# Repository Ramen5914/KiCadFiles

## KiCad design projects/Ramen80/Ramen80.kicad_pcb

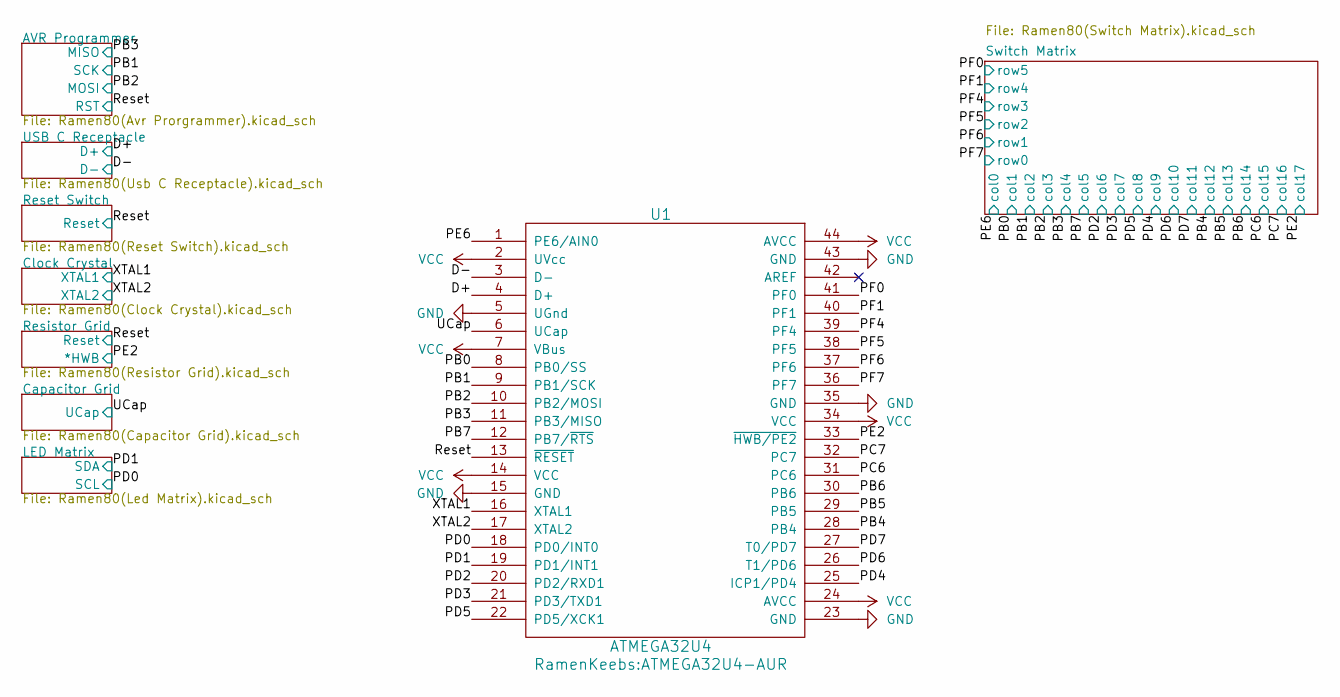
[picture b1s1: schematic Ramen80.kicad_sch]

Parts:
U1: ATMEGA32U4; ATMEGA32U4-AUR

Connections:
/D+: U1.4 (D+); also elsewhere on the board
/D-: U1.3 (D-); also elsewhere on the board
/PB0: U1.8 (PB0/SS); also elsewhere on the board
/PB1: U1.9 (PB1/SCK); also elsewhere on the board
/PB2: U1.10 (PB2/MOSI); also elsewhere on the board
/PB3: U1.11 (PB3/MISO); also elsewhere on the board
/PB4: U1.28 (PB4); also elsewhere on the board
/PB5: U1.29 (PB5); also elsewhere on the board
/PB6: U1.30 (PB6); also elsewhere on the board
/PB7: U1.12 (PB7/~RTS); also elsewhere on the board
/PC6: U1.31 (PC6); also elsewhere on the board
/PC7: U1.32 (PC7); also elsewhere on the board
/PD0: U1.18 (PD0/INT0); also elsewhere on the board
/PD1: U1.19 (PD1/INT1); also elsewhere on the board
/PD2: U1.20 (PD2/RXD1); also elsewhere on the board
/PD3: U1.21 (PD3/TXD1); also elsewhere on the board
/PD4: U1.25 (ICP1/PD4); also elsewhere on the board
/PD5: U1.22 (PD5/XCK1); also elsewhere on the board
/PD6: U1.26 (T1/PD6); also elsewhere on the board
/PD7: U1.27 (T0/PD7); also elsewhere on the board
/PE2: U1.33 (~HWB/PE2); also elsewhere on the board
/PE6: U1.1 (PE6/AIN0); also elsewhere on the board
/PF0: U1.41 (PF0); also elsewhere on the board
/PF1: U1.40 (PF1); also elsewhere on the board
/PF4: U1.39 (PF4); also elsewhere on the board
/PF5: U1.38 (PF5); also elsewhere on the board
/PF6: U1.37 (PF6); also elsewhere on the board
/PF7: U1.36 (PF7); also elsewhere on the board
/Reset: U1.13 (~RESET); also elsewhere on the board
/UCap: U1.6 (UCap); also elsewhere on the board
/XTAL1: U1.16 (XTAL1); also elsewhere on the board
/XTAL2: U1.17 (XTAL2); also elsewhere on the board
GND: U1.5 (UGnd), U1.15 (GND), U1.23 (GND), U1.35 (GND), U1.43 (GND); also elsewhere on the board
VCC: U1.2 (UVcc), U1.7 (VBus), U1.14 (VCC), U1.24 (AVCC), U1.34 (VCC), U1.44 (AVCC); also elsewhere on the board

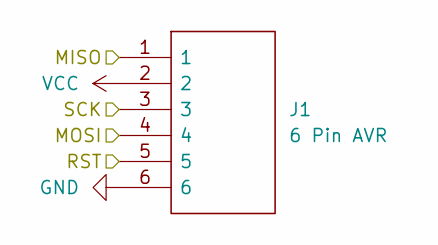
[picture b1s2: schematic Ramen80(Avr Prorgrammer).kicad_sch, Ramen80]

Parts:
J1: 6 Pin AVR; RHDR6W30P0X100_1X6_650X150X210P

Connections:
/PB1: J1.3; also elsewhere on the board
/PB2: J1.4; also elsewhere on the board
/PB3: J1.1; also elsewhere on the board
/Reset: J1.5; also elsewhere on the board
GND: J1.6; also elsewhere on the board
VCC: J1.2; also elsewhere on the board

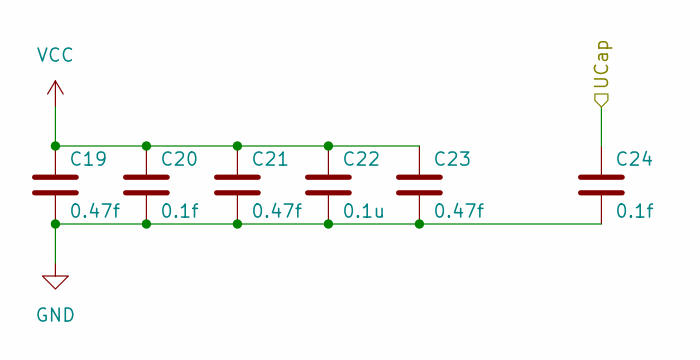
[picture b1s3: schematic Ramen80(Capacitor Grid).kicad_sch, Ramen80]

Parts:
C19, C21, C23: 0.47f; C_0805
C20, C24: 0.1f; C_0805
C22: 0.1u; C_0805

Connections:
/UCap: C24.1; also elsewhere on the board
GND: C19.2, C20.2, C21.2, C22.2, C23.2, C24.2; also elsewhere on the board
VCC: C19.1, C20.1, C21.1, C22.1, C23.1; also elsewhere on the board

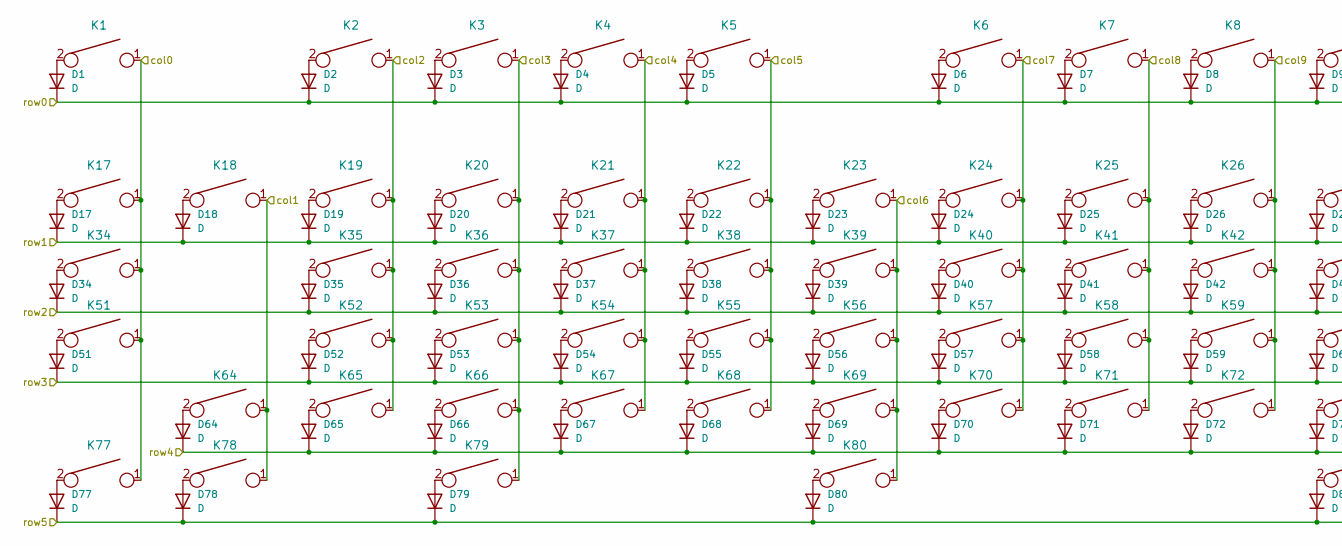
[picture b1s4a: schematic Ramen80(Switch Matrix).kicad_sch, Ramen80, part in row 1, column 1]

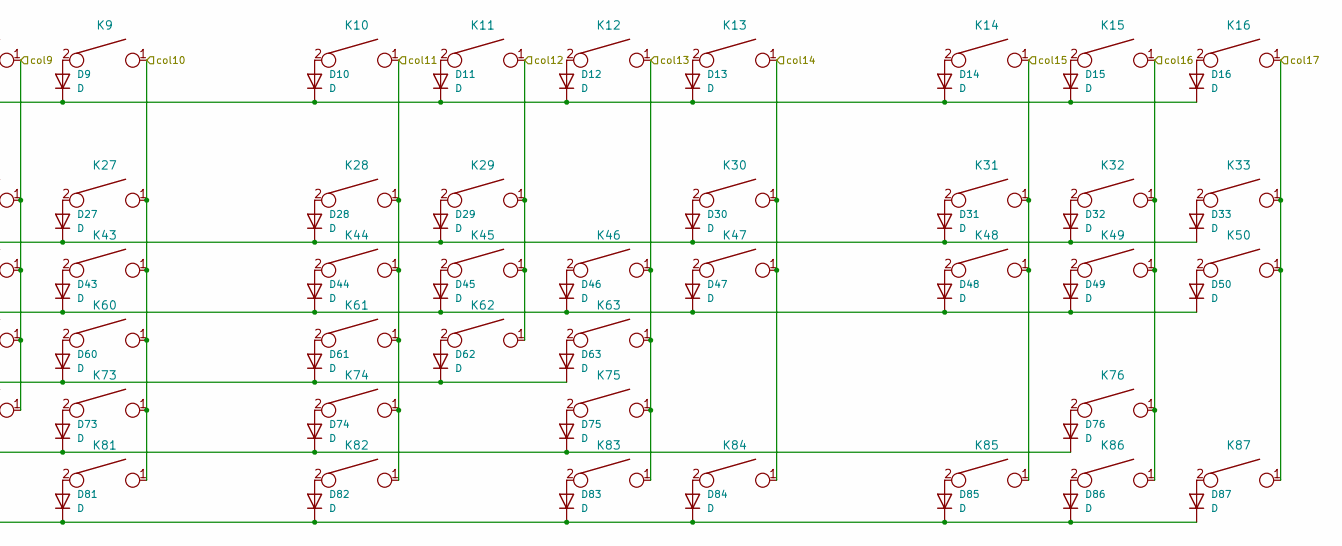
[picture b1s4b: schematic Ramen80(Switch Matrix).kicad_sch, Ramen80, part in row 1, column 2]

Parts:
D1, D2, D3, D4, D5, D6, D7, D8, D9, D10, D11, D12, D13, D14, D15, D16, D17, D18, D19, D20, D21, D22, D23, D24, D25, D26, D27, D28, D29, D30, D31, D32, D33, D34, D35, D36, D37, D38, D39, D40, D41, D42, D43, D44, D45, D46, D47, D48, D49, D50, D51, D52, D53, D54, D55, D56, D57, D58, D59, D60, D61, D62, D63, D64, D65, D66, D67, D68, D69, D70, D71, D72, D73, D74, D75, D76, D77, D78, D79, D80, D81, D82, D83, D84, D85, D86, D87: D; D_AXIAL
K1, K2, K3, K4, K5, K6, K7, K8, K9, K10, K11, K12, K13, K14, K15, K16, K17, K18, K19, K20, K21, K22, K23, K24, K25, K26, K27, K28, K29, K30, K31, K32, K33, K34, K35, K36, K37, K38, K39, K40, K41, K42, K43, K44, K45, K46, K47, K48, K49, K50, K51, K52, K53, K54, K55, K56, K57, K58, K59, K60, K61, K62, K63, K64, K65, K66, K67, K68, K69, K70, K71, K72, K73, K74, K75, K76, K77, K78, K79, K80, K81, K82, K83, K84, K85, K86, K87: KEYSW; KAILH_PLATEMOUNT

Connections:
/PB0: K18.1, K64.1, K78.1; also elsewhere on the board
/PB1: K2.1, K19.1, K35.1, K52.1, K65.1; also elsewhere on the board
/PB2: K3.1, K20.1, K36.1, K53.1, K66.1, K79.1; also elsewhere on the board
/PB3: K4.1, K21.1, K37.1, K54.1, K67.1; also elsewhere on the board
/PB4: K11.1, K29.1, K45.1, K62.1; also elsewhere on the board
/PB5: K12.1, K46.1, K63.1, K75.1, K83.1; also elsewhere on the board
/PB6: K13.1, K30.1, K47.1, K84.1; also elsewhere on the board
/PB7: K5.1, K22.1, K38.1, K55.1, K68.1; also elsewhere on the board
/PC6: K14.1, K31.1, K48.1, K85.1; also elsewhere on the board
/PC7: K15.1, K32.1, K49.1, K76.1, K86.1; also elsewhere on the board
/PD2: K23.1, K39.1, K56.1, K69.1, K80.1; also elsewhere on the board
/PD3: K6.1, K24.1, K40.1, K57.1, K70.1; also elsewhere on the board
/PD4: K8.1, K26.1, K42.1, K59.1, K72.1; also elsewhere on the board
/PD5: K7.1, K25.1, K41.1, K58.1, K71.1; also elsewhere on the board
/PD6: K9.1, K27.1, K43.1, K60.1, K73.1, K81.1; also elsewhere on the board
/PD7: K10.1, K28.1, K44.1, K61.1, K74.1, K82.1; also elsewhere on the board
/PE2: K16.1, K33.1, K50.1, K87.1; also elsewhere on the board
/PE6: K1.1, K17.1, K34.1, K51.1, K77.1; also elsewhere on the board
/PF0: D77.1 (K), D78.1 (K), D79.1 (K), D80.1 (K), D81.1 (K), D82.1 (K), D83.1 (K), D84.1 (K), D85.1 (K), D86.1 (K), D87.1 (K); also elsewhere on the board
/PF1: D64.1 (K), D65.1 (K), D66.1 (K), D67.1 (K), D68.1 (K), D69.1 (K), D70.1 (K), D71.1 (K), D72.1 (K), D73.1 (K), D74.1 (K), D75.1 (K), D76.1 (K); also elsewhere on the board
/PF4: D51.1 (K), D52.1 (K), D53.1 (K), D54.1 (K), D55.1 (K), D56.1 (K), D57.1 (K), D58.1 (K), D59.1 (K), D60.1 (K), D61.1 (K), D62.1 (K), D63.1 (K); also elsewhere on the board
/PF5: D34.1 (K), D35.1 (K), D36.1 (K), D37.1 (K), D38.1 (K), D39.1 (K), D40.1 (K), D41.1 (K), D42.1 (K), D43.1 (K), D44.1 (K), D45.1 (K), D46.1 (K), D47.1 (K), D48.1 (K), D49.1 (K), D50.1 (K); also elsewhere on the board
/PF6: D17.1 (K), D18.1 (K), D19.1 (K), D20.1 (K), D21.1 (K), D22.1 (K), D23.1 (K), D24.1 (K), D25.1 (K), D26.1 (K), D27.1 (K), D28.1 (K), D29.1 (K), D30.1 (K), D31.1 (K), D32.1 (K), D33.1 (K); also elsewhere on the board
/PF7: D1.1 (K), D2.1 (K), D3.1 (K), D4.1 (K), D5.1 (K), D6.1 (K), D7.1 (K), D8.1 (K), D9.1 (K), D10.1 (K), D11.1 (K), D12.1 (K), D13.1 (K), D14.1 (K), D15.1 (K), D16.1 (K); also elsewhere on the board
unnamed: D1.2 (A), K1.2
unnamed: D2.2 (A), K2.2
unnamed: D3.2 (A), K3.2
unnamed: D4.2 (A), K4.2
unnamed: D5.2 (A), K5.2
unnamed: D6.2 (A), K6.2
unnamed: D7.2 (A), K7.2
unnamed: D8.2 (A), K8.2
unnamed: D9.2 (A), K9.2
unnamed: D10.2 (A), K10.2
unnamed: D11.2 (A), K11.2
unnamed: D12.2 (A), K12.2
unnamed: D13.2 (A), K13.2
unnamed: D14.2 (A), K14.2
unnamed: D15.2 (A), K15.2
unnamed: D16.2 (A), K16.2
unnamed: D17.2 (A), K17.2
unnamed: D18.2 (A), K18.2
unnamed: D19.2 (A), K19.2
unnamed: D20.2 (A), K20.2
unnamed: D21.2 (A), K21.2
unnamed: D22.2 (A), K22.2
unnamed: D23.2 (A), K23.2
unnamed: D24.2 (A), K24.2
unnamed: D25.2 (A), K25.2
unnamed: D26.2 (A), K26.2
unnamed: D27.2 (A), K27.2
unnamed: D28.2 (A), K28.2
unnamed: D29.2 (A), K29.2
unnamed: D30.2 (A), K30.2
unnamed: D31.2 (A), K31.2
unnamed: D32.2 (A), K32.2
unnamed: D33.2 (A), K33.2
unnamed: D34.2 (A), K34.2
unnamed: D35.2 (A), K35.2
unnamed: D36.2 (A), K36.2
unnamed: D37.2 (A), K37.2
unnamed: D38.2 (A), K38.2
unnamed: D39.2 (A), K39.2
unnamed: D40.2 (A), K40.2
unnamed: D41.2 (A), K41.2
unnamed: D42.2 (A), K42.2
unnamed: D43.2 (A), K43.2
unnamed: D44.2 (A), K44.2
unnamed: D45.2 (A), K45.2
unnamed: D46.2 (A), K46.2
unnamed: D47.2 (A), K47.2
unnamed: D48.2 (A), K48.2
unnamed: D49.2 (A), K49.2
unnamed: D50.2 (A), K50.2
unnamed: D51.2 (A), K51.2
unnamed: D52.2 (A), K52.2
unnamed: D53.2 (A), K53.2
unnamed: D54.2 (A), K54.2
unnamed: D55.2 (A), K55.2
unnamed: D56.2 (A), K56.2
unnamed: D57.2 (A), K57.2
unnamed: D58.2 (A), K58.2
unnamed: D59.2 (A), K59.2
unnamed: D60.2 (A), K60.2
unnamed: D61.2 (A), K61.2
unnamed: D62.2 (A), K62.2
unnamed: D63.2 (A), K63.2
unnamed: D64.2 (A), K64.2
unnamed: D65.2 (A), K65.2
unnamed: D66.2 (A), K66.2
unnamed: D67.2 (A), K67.2
unnamed: D68.2 (A), K68.2
unnamed: D69.2 (A), K69.2
unnamed: D70.2 (A), K70.2
unnamed: D71.2 (A), K71.2
unnamed: D72.2 (A), K72.2
unnamed: D73.2 (A), K73.2
unnamed: D74.2 (A), K74.2
unnamed: D75.2 (A), K75.2
unnamed: D76.2 (A), K76.2
unnamed: D77.2 (A), K77.2
unnamed: D78.2 (A), K78.2
unnamed: D79.2 (A), K79.2
unnamed: D80.2 (A), K80.2
unnamed: D81.2 (A), K81.2
unnamed: D82.2 (A), K82.2
unnamed: D83.2 (A), K83.2
unnamed: D84.2 (A), K84.2
unnamed: D85.2 (A), K85.2
unnamed: D86.2 (A), K86.2
unnamed: D87.2 (A), K87.2

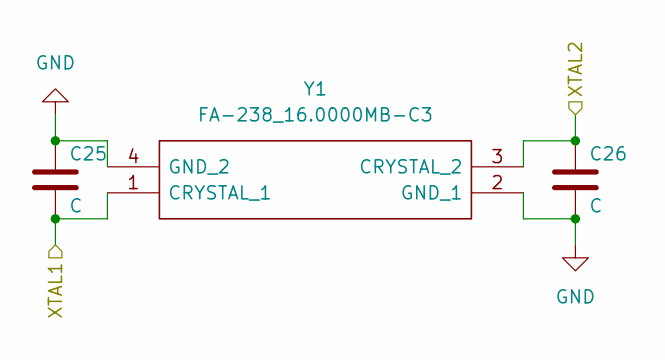
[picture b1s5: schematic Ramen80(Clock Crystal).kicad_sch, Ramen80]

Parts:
C25, C26: C; C_0805
Y1: FA-238_16.0000MB-C3; FA238160000MBC3; Manufacturer_Part_Number FA-238 16.0000MB-C3; Mouser Part Number 732-FA-23816B-C3

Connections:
/XTAL1: C25.2, Y1.1 (CRYSTAL_1); also elsewhere on the board
/XTAL2: C26.1, Y1.3 (CRYSTAL_2); also elsewhere on the board
GND: C25.1, C26.2, Y1.2 (GND_1), Y1.4 (GND_2); also elsewhere on the board

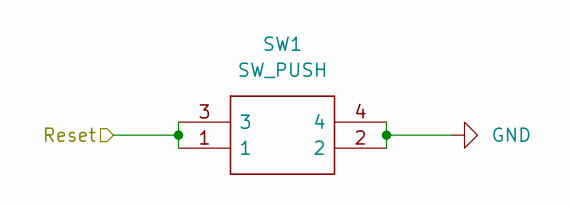
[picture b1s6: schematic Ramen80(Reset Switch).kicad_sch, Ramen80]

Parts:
SW1: SW_PUSH; TL3342F160QG

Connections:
/Reset: SW1.1, SW1.3; also elsewhere on the board
GND: SW1.2, SW1.4; also elsewhere on the board

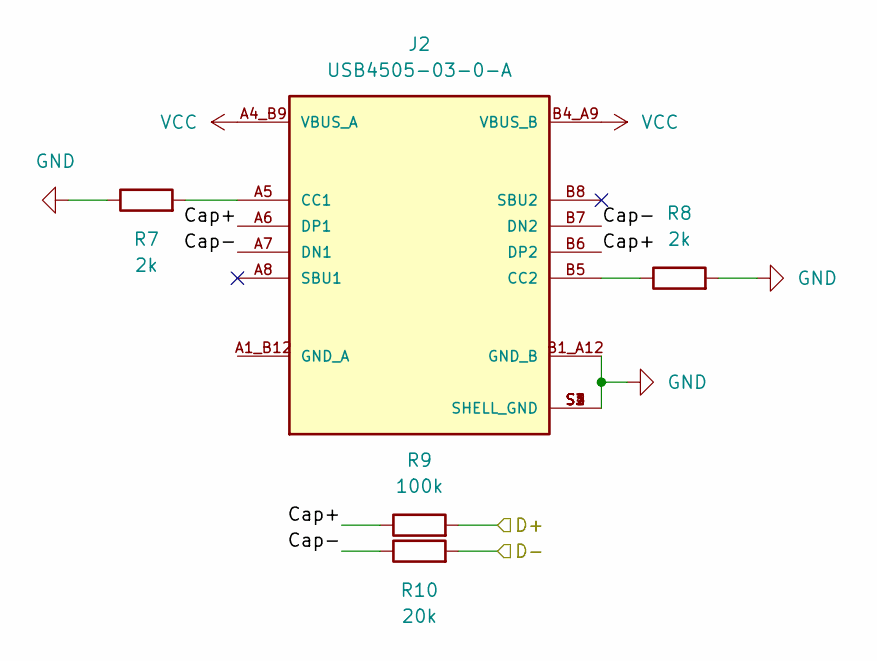
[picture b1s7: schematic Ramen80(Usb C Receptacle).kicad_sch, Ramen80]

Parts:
J2: USB4505-03-0-A
R7, R8: 2k; R_0805
R9: 100k; R_0805
R10: 20k; R_0805

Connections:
/D+: R9.2; also elsewhere on the board
/D-: R10.2; also elsewhere on the board
/USB C Receptacle/Cap+: J2.A6 (DP1), J2.B6 (DP2), R9.1
/USB C Receptacle/Cap-: J2.A7 (DN1), J2.B7 (DN2), R10.1
GND: J2.B1_A12 (GND_B), J2.S1 (SHELL_GND), J2.S2 (SHELL_GND), J2.S3 (SHELL_GND), J2.S4 (SHELL_GND), R7.1, R8.2; also elsewhere on the board
unnamed: J2.A5 (CC1), R7.2
unnamed: J2.B5 (CC2), R8.1
VCC: J2.A4_B9 (VBUS_A), J2.B4_A9 (VBUS_B); also elsewhere on the board

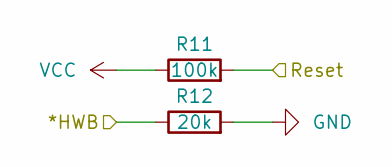
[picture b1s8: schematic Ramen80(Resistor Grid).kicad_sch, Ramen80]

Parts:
R11: 100k; R_0805
R12: 20k; R_0805

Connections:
/PE2: R12.1; also elsewhere on the board
/Reset: R11.2; also elsewhere on the board
GND: R12.2; also elsewhere on the board
VCC: R11.1; also elsewhere on the board

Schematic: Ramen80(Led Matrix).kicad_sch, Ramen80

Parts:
C1, C3, C8, C10, C11, C14, C17: 0.47f; C_0805
C2, C6, C7, C12, C15, C18: 0.1f; C_0805
C4: 4.7u; C_0805
C5, C9, C13: 0.1u; C_0805
C16: 1u; C_0805
LED1, LED2, LED3, LED4, LED5, LED6, LED7, LED8, LED9, LED10, LED11, LED12, LED13, LED14, LED15, LED16, LED17, LED18, LED19, LED20, LED21, LED22, LED23, LED24, LED25, LED26, LED27, LED28, LED29, LED30, LED31, LED32, LED33, LED34, LED35, LED36, LED37, LED38, LED39, LED40, LED41, LED42, LED43, LED44, LED45, LED46, LED47, LED48, LED49, LED50, LED51, LED52, LED53, LED54, LED55, LED56, LED57, LED58, LED59, LED60, LED61, LED62, LED63, LED64, LED65, LED66, LED67, LED68, LED69, LED70, LED71, LED72, LED73, LED74, LED75, LED76, LED77, LED78, LED79, LED80, LED81, LED82, LED83, LED84, LED85, LED86, LED87: RGB_LED; QBLP677R-RGB
R1, R3: 5k1; R_0805
R2, R4: 22; R_0805
R5, R6: 10k; R_0805
U2, U3: IS31FL3733-TQ; TQFP-48-1EP_7x7mm_P0.5mm_EP5x5mm

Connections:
/LED Matrix/2CS1: LED9.4 (VCC), LED42.4 (VCC), LED72.4 (VCC), U3.16 (CS1)
/LED Matrix/2CS2: LED10.4 (VCC), LED43.4 (VCC), LED73.4 (VCC), U3.17 (CS2)
/LED Matrix/2CS3: LED11.4 (VCC), LED44.4 (VCC), LED74.4 (VCC), U3.18 (CS3)
/LED Matrix/2CS4: LED12.4 (VCC), LED45.4 (VCC), LED75.4 (VCC), U3.19 (CS4)
/LED Matrix/2CS5: LED13.4 (VCC), LED46.4 (VCC), U3.21 (CS5)
/LED Matrix/2CS6: LED14.4 (VCC), LED47.4 (VCC), U3.22 (CS6)
/LED Matrix/2CS7: LED15.4 (VCC), LED48.4 (VCC), LED76.4 (VCC), U3.23 (CS7)
/LED Matrix/2CS8: LED16.4 (VCC), LED49.4 (VCC), U3.24 (CS8)
/LED Matrix/2CS9: LED25.4 (VCC), LED59.4 (VCC), LED81.4 (VCC), U3.25 (CS9)
/LED Matrix/2CS10: LED26.4 (VCC), LED60.4 (VCC), LED82.4 (VCC), U3.26 (CS10)
/LED Matrix/2CS11: LED27.4 (VCC), LED61.4 (VCC), LED83.4 (VCC), U3.27 (CS11)
/LED Matrix/2CS12: LED28.4 (VCC), LED62.4 (VCC), LED84.4 (VCC), U3.28 (CS12)
/LED Matrix/2CS13: LED29.4 (VCC), LED63.4 (VCC), LED85.4 (VCC), U3.30 (CS13)
/LED Matrix/2CS14: LED30.4 (VCC), LED50.4 (VCC), U3.31 (CS14)
/LED Matrix/2CS15: LED31.4 (VCC), LED33.4 (VCC), LED86.4 (VCC), U3.32 (CS15)
/LED Matrix/2CS16: LED32.4 (VCC), LED87.4 (VCC), U3.33 (CS16)
/LED Matrix/2SW1: LED9.2 (G), LED10.2 (G), LED11.2 (G), LED12.2 (G), LED13.2 (G), LED14.2 (G), LED15.2 (G), LED16.2 (G), LED25.2 (G), LED26.2 (G), LED27.2 (G), LED28.2 (G), LED29.2 (G), LED30.2 (G), LED31.2 (G), LED32.2 (G), U3.2 (SW1)
/LED Matrix/2SW2: LED9.3 (R), LED10.3 (R), LED11.3 (R), LED12.3 (R), LED13.3 (R), LED14.3 (R), LED15.3 (R), LED16.3 (R), LED25.3 (R), LED26.3 (R), LED27.3 (R), LED28.3 (R), LED29.3 (R), LED30.3 (R), LED31.3 (R), LED32.3 (R), U3.3 (SW2)
/LED Matrix/2SW3: LED9.1 (B), LED10.1 (B), LED11.1 (B), LED12.1 (B), LED13.1 (B), LED14.1 (B), LED15.1 (B), LED16.1 (B), LED25.1 (B), LED26.1 (B), LED27.1 (B), LED28.1 (B), LED29.1 (B), LED30.1 (B), LED31.1 (B), LED32.1 (B), U3.4 (SW3)
/LED Matrix/2SW4: LED33.2 (G), LED42.2 (G), LED43.2 (G), LED44.2 (G), LED45.2 (G), LED46.2 (G), LED47.2 (G), LED48.2 (G), LED49.2 (G), LED50.2 (G), LED59.2 (G), LED60.2 (G), LED61.2 (G), LED62.2 (G), LED63.2 (G), U3.6 (SW4)
/LED Matrix/2SW5: LED33.3 (R), LED42.3 (R), LED43.3 (R), LED44.3 (R), LED45.3 (R), LED46.3 (R), LED47.3 (R), LED48.3 (R), LED49.3 (R), LED50.3 (R), LED59.3 (R), LED60.3 (R), LED61.3 (R), LED62.3 (R), LED63.3 (R), U3.7 (SW5)
/LED Matrix/2SW6: LED33.1 (B), LED42.1 (B), LED43.1 (B), LED44.1 (B), LED45.1 (B), LED46.1 (B), LED47.1 (B), LED48.1 (B), LED49.1 (B), LED50.1 (B), LED59.1 (B), LED60.1 (B), LED61.1 (B), LED62.1 (B), LED63.1 (B), U3.8 (SW6)
/LED Matrix/2SW7: LED72.2 (G), LED73.2 (G), LED74.2 (G), LED75.2 (G), LED76.2 (G), LED81.2 (G), LED82.2 (G), LED83.2 (G), LED84.2 (G), LED85.2 (G), LED86.2 (G), LED87.2 (G), U3.9 (SW7)
/LED Matrix/2SW8: LED72.3 (R), LED73.3 (R), LED74.3 (R), LED75.3 (R), LED76.3 (R), LED81.3 (R), LED82.3 (R), LED83.3 (R), LED84.3 (R), LED85.3 (R), LED86.3 (R), LED87.3 (R), U3.10 (SW8)
/LED Matrix/2SW9: LED72.1 (B), LED73.1 (B), LED74.1 (B), LED75.1 (B), LED76.1 (B), LED81.1 (B), LED82.1 (B), LED83.1 (B), LED84.1 (B), LED85.1 (B), LED86.1 (B), LED87.1 (B), U3.11 (SW9)
/LED Matrix/CS1: LED1.4 (VCC), LED34.4 (VCC), LED64.4 (VCC), U2.16 (CS1)
/LED Matrix/CS2: LED2.4 (VCC), LED35.4 (VCC), LED65.4 (VCC), U2.17 (CS2)
/LED Matrix/CS3: LED3.4 (VCC), LED36.4 (VCC), LED66.4 (VCC), U2.18 (CS3)
/LED Matrix/CS4: LED4.4 (VCC), LED37.4 (VCC), LED67.4 (VCC), U2.19 (CS4)
/LED Matrix/CS5: LED5.4 (VCC), LED38.4 (VCC), LED68.4 (VCC), U2.21 (CS5)
/LED Matrix/CS6: LED6.4 (VCC), LED39.4 (VCC), LED69.4 (VCC), U2.22 (CS6)
/LED Matrix/CS7: LED7.4 (VCC), LED40.4 (VCC), LED70.4 (VCC), U2.23 (CS7)
/LED Matrix/CS8: LED8.4 (VCC), LED41.4 (VCC), LED71.4 (VCC), U2.24 (CS8)
/LED Matrix/CS9: LED17.4 (VCC), LED51.4 (VCC), LED77.4 (VCC), U2.25 (CS9)
/LED Matrix/CS10: LED18.4 (VCC), LED52.4 (VCC), LED78.4 (VCC), U2.26 (CS10)
/LED Matrix/CS11: LED19.4 (VCC), LED53.4 (VCC), LED79.4 (VCC), U2.27 (CS11)
/LED Matrix/CS12: LED20.4 (VCC), LED54.4 (VCC), U2.28 (CS12)
/LED Matrix/CS13: LED21.4 (VCC), LED55.4 (VCC), U2.30 (CS13)
/LED Matrix/CS14: LED22.4 (VCC), LED56.4 (VCC), LED80.4 (VCC), U2.31 (CS14)
/LED Matrix/CS15: LED23.4 (VCC), LED57.4 (VCC), U2.32 (CS15)
/LED Matrix/CS16: LED24.4 (VCC), LED58.4 (VCC), U2.33 (CS16)
/LED Matrix/SW1: LED1.2 (G), LED2.2 (G), LED3.2 (G), LED4.2 (G), LED5.2 (G), LED6.2 (G), LED7.2 (G), LED8.2 (G), LED17.2 (G), LED18.2 (G), LED19.2 (G), LED20.2 (G), LED21.2 (G), LED22.2 (G), LED23.2 (G), LED24.2 (G), U2.2 (SW1)
/LED Matrix/SW2: LED1.3 (R), LED2.3 (R), LED3.3 (R), LED4.3 (R), LED5.3 (R), LED6.3 (R), LED7.3 (R), LED8.3 (R), LED17.3 (R), LED18.3 (R), LED19.3 (R), LED20.3 (R), LED21.3 (R), LED22.3 (R), LED23.3 (R), LED24.3 (R), U2.3 (SW2)
/LED Matrix/SW3: LED1.1 (B), LED2.1 (B), LED3.1 (B), LED4.1 (B), LED5.1 (B), LED6.1 (B), LED7.1 (B), LED8.1 (B), LED17.1 (B), LED18.1 (B), LED19.1 (B), LED20.1 (B), LED21.1 (B), LED22.1 (B), LED23.1 (B), LED24.1 (B), U2.4 (SW3)
/LED Matrix/SW4: LED34.2 (G), LED35.2 (G), LED36.2 (G), LED37.2 (G), LED38.2 (G), LED39.2 (G), LED40.2 (G), LED41.2 (G), LED51.2 (G), LED52.2 (G), LED53.2 (G), LED54.2 (G), LED55.2 (G), LED56.2 (G), LED57.2 (G), LED58.2 (G), U2.6 (SW4)
/LED Matrix/SW5: LED34.3 (R), LED35.3 (R), LED36.3 (R), LED37.3 (R), LED38.3 (R), LED39.3 (R), LED40.3 (R), LED41.3 (R), LED51.3 (R), LED52.3 (R), LED53.3 (R), LED54.3 (R), LED55.3 (R), LED56.3 (R), LED57.3 (R), LED58.3 (R), U2.7 (SW5)
/LED Matrix/SW6: LED34.1 (B), LED35.1 (B), LED36.1 (B), LED37.1 (B), LED38.1 (B), LED39.1 (B), LED40.1 (B), LED41.1 (B), LED51.1 (B), LED52.1 (B), LED53.1 (B), LED54.1 (B), LED55.1 (B), LED56.1 (B), LED57.1 (B), LED58.1 (B), U2.8 (SW6)
/LED Matrix/SW7: LED64.2 (G), LED65.2 (G), LED66.2 (G), LED67.2 (G), LED68.2 (G), LED69.2 (G), LED70.2 (G), LED71.2 (G), LED77.2 (G), LED78.2 (G), LED79.2 (G), LED80.2 (G), U2.9 (SW7)
/LED Matrix/SW8: LED64.3 (R), LED65.3 (R), LED66.3 (R), LED67.3 (R), LED68.3 (R), LED69.3 (R), LED70.3 (R), LED71.3 (R), LED77.3 (R), LED78.3 (R), LED79.3 (R), LED80.3 (R), U2.10 (SW8)
/LED Matrix/SW9: LED64.1 (B), LED65.1 (B), LED66.1 (B), LED67.1 (B), LED68.1 (B), LED69.1 (B), LED70.1 (B), LED71.1 (B), LED77.1 (B), LED78.1 (B), LED79.1 (B), LED80.1 (B), U2.11 (SW9)
/LED Matrix/Sync: U2.40 (SYNC), U3.40 (SYNC)
/PD0: R4.2, U2.42 (SCL), U3.42 (SCL); also elsewhere on the board
/PD1: R3.2, U2.41 (SDA), U3.41 (SDA); also elsewhere on the board
GND: C1.2, C2.2, C3.2, C4.2, C5.2, C6.2, C7.2, C8.2, C9.2, C10.2, C11.2, C12.2, C13.2, C14.2, C15.2, C16.2, C17.2, C18.2, R1.1, R2.2, R5.1, R6.2, U2.5 (PGND), U2.12 (PGND), U2.34 (AGND), U2.43 (ADDR1), U2.44 (ADDR2), U2.48 (GND), U2.49 (GND), U3.5 (PGND), U3.12 (PGND), U3.34 (AGND), U3.44 (ADDR2), U3.48 (GND), U3.49 (GND); also elsewhere on the board
unnamed: R1.2, U2.47 (IICRST)
unnamed: R2.1, U2.35 (RSET)
unnamed: R5.2, U3.47 (IICRST)
unnamed: R6.1, U3.35 (RSET)
VCC: C1.1, C2.1, C3.1, C4.1, C5.1, C6.1, C7.1, C8.1, C9.1, C10.1, C11.1, C12.1, C13.1, C14.1, C15.1, C16.1, C17.1, C18.1, R3.1, R4.1, U2.20 (PVCC), U2.29 (PVCC), U2.37 (AVCC), U2.38 (DVCC), U2.39 (VIO), U2.46 (~SDB), U3.20 (PVCC), U3.29 (PVCC), U3.37 (AVCC), U3.38 (DVCC), U3.39 (VIO), U3.43 (ADDR1), U3.46 (~SDB); also elsewhere on the board

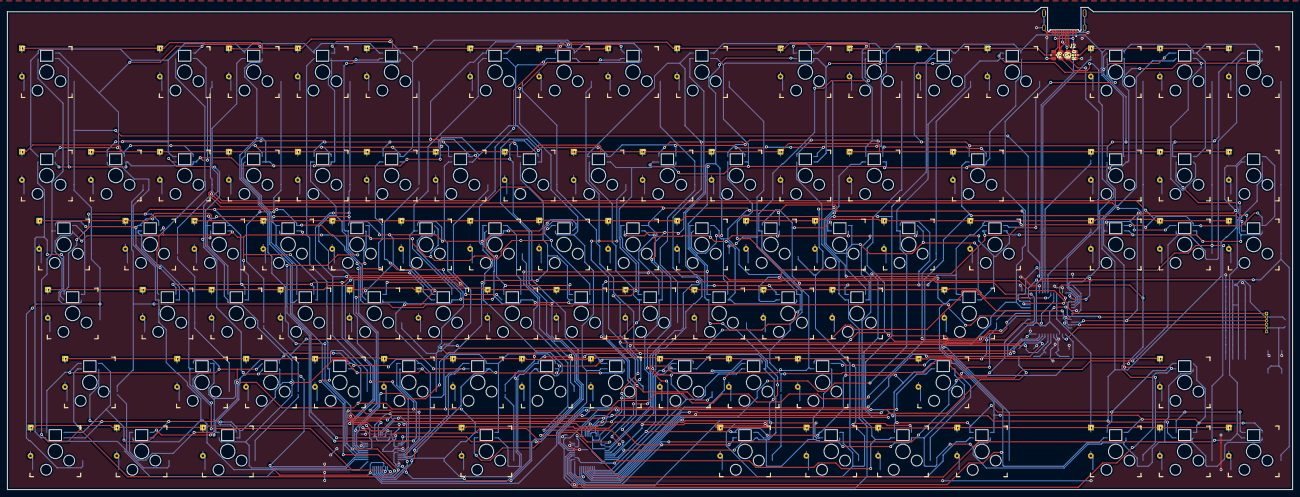
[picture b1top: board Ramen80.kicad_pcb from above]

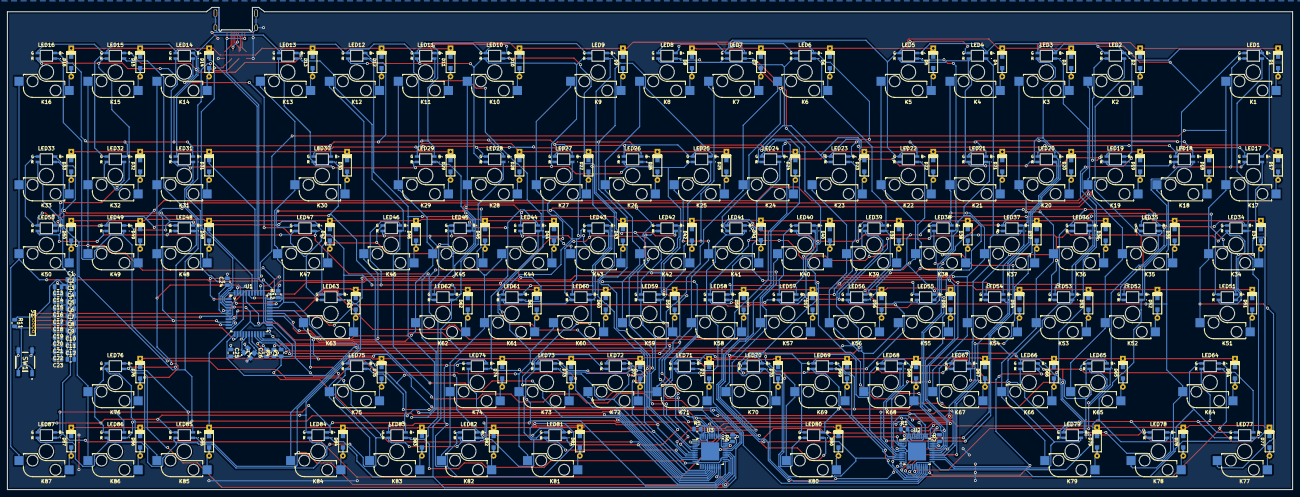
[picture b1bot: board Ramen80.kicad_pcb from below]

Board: 2 copper layers, 355.0 x 133.2 mm, 306 parts (214 on the bottom side), 180 nets.

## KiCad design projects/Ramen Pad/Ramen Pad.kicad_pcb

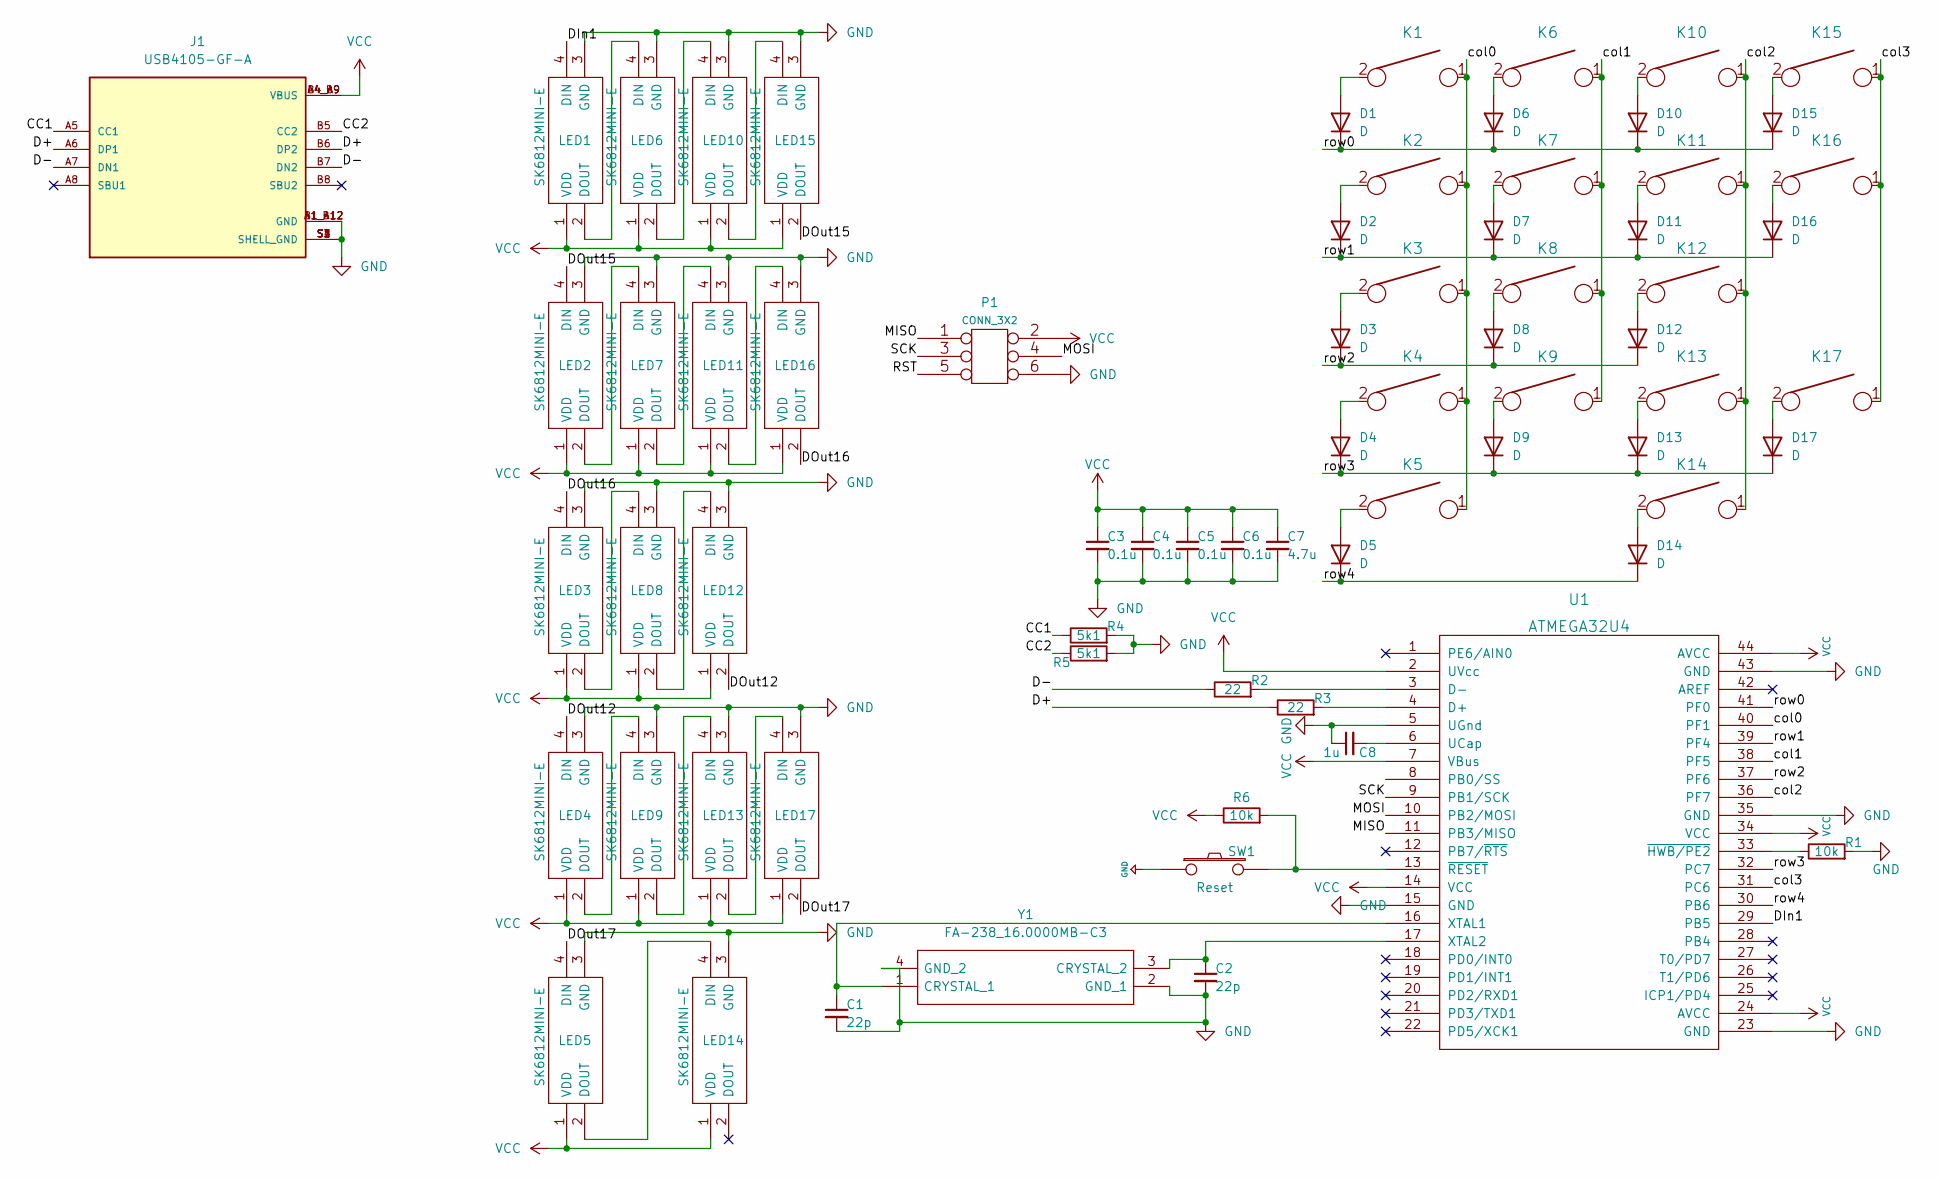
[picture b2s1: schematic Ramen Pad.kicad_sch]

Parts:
C1, C2: 22p; C_0805_2012Metric_Pad1.18x1.45mm_HandSolder
C3, C4, C5, C6: 0.1u; C_0805_2012Metric_Pad1.18x1.45mm_HandSolder
C7: 4.7u; C_0805_2012Metric_Pad1.18x1.45mm_HandSolder
C8: 1u; C_0805_2012Metric_Pad1.18x1.45mm_HandSolder
D1, D2, D3, D4, D5, D6, D7, D8, D9, D10, D11, D12, D13, D14, D15, D16, D17: D; D_SOD123_axial
J1: USB4105-GF-A; GCT_USB4105-GF-A; PARTREV A3
K1, K2, K3, K4, K5, K6, K7, K8, K9, K10, K11, K12, K13, K14, K15, K16, K17: KEYSW; Kailh_socket_MX_platemount
LED1, LED2, LED3, LED4, LED5, LED6, LED7, LED8, LED9, LED10, LED11, LED12, LED13, LED14, LED15, LED16, LED17: SK6812MINI-E; SK6812-MINI-E; Manufacturer_Part_Number SK6812MINI-E
P1: CONN_3X2; PinSocket_1x06_P1.00mm_Vertical
R1, R6: 10k; R_0805_2012Metric_Pad1.20x1.40mm_HandSolder
R2, R3: 22; R_0805_2012Metric_Pad1.20x1.40mm_HandSolder
R4, R5: 5k1; R_0805_2012Metric_Pad1.20x1.40mm_HandSolder
SW1: Reset; SW_SPST_TL3342
U1: ATMEGA32U4; TQFP-44_10x10mm_P0.8mm
Y1: FA-238_16.0000MB-C3; FA238160000MBC3; Manufacturer_Part_Number FA-238 16.0000MB-C3; Mouser Part Number 732-FA-23816B-C3

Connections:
/CC1: J1.A5 (CC1), R4.1
/CC2: J1.B5 (CC2), R5.1
/D+: J1.A6 (DP1), J1.B6 (DP2), R3.1
/D-: J1.A7 (DN1), J1.B7 (DN2), R2.1
/DIn1: LED1.4 (DIN), U1.29 (PB5)
/DOut12: LED4.4 (DIN), LED12.2 (DOUT)
/DOut15: LED2.4 (DIN), LED15.2 (DOUT)
/DOut16: LED3.4 (DIN), LED16.2 (DOUT)
/DOut17: LED5.4 (DIN), LED17.2 (DOUT)
/MISO: P1.1, U1.11 (PB3/MISO)
/MOSI: P1.4, U1.10 (PB2/MOSI)
/RST: P1.5
/SCK: P1.3, U1.9 (PB1/SCK)
/col0: K1.1, K2.1, K3.1, K4.1, K5.1, U1.40 (PF1)
/col1: K6.1, K7.1, K8.1, K9.1, U1.38 (PF5)
/col2: K10.1, K11.1, K12.1, K13.1, K14.1, U1.36 (PF7)
/col3: K15.1, K16.1, K17.1, U1.31 (PC6)
/row0: D1.1 (K), D6.1 (K), D10.1 (K), D15.1 (K), U1.41 (PF0)
/row1: D2.1 (K), D7.1 (K), D11.1 (K), D16.1 (K), U1.39 (PF4)
/row2: D3.1 (K), D8.1 (K), D12.1 (K), U1.37 (PF6)
/row3: D4.1 (K), D9.1 (K), D13.1 (K), D17.1 (K), U1.32 (PC7)
/row4: D5.1 (K), D14.1 (K), U1.30 (PB6)
unnamed: C1.1, U1.16 (XTAL1), Y1.1 (CRYSTAL_1)
unnamed: C2.1, U1.17 (XTAL2), Y1.3 (CRYSTAL_2)
unnamed: C8.2, U1.6 (UCap)
unnamed: D1.2 (A), K1.2
unnamed: D2.2 (A), K2.2
unnamed: D3.2 (A), K3.2
unnamed: D4.2 (A), K4.2
unnamed: D5.2 (A), K5.2
unnamed: D6.2 (A), K6.2
unnamed: D7.2 (A), K7.2
unnamed: D8.2 (A), K8.2
unnamed: D9.2 (A), K9.2
unnamed: D10.2 (A), K10.2
unnamed: D11.2 (A), K11.2
unnamed: D12.2 (A), K12.2
unnamed: D13.2 (A), K13.2
unnamed: D14.2 (A), K14.2
unnamed: D15.2 (A), K15.2
unnamed: D16.2 (A), K16.2
unnamed: D17.2 (A), K17.2
unnamed: LED1.2 (DOUT), LED6.4 (DIN)
unnamed: LED2.2 (DOUT), LED7.4 (DIN)
unnamed: LED3.2 (DOUT), LED8.4 (DIN)
unnamed: LED4.2 (DOUT), LED9.4 (DIN)
unnamed: LED10.2 (DOUT), LED15.4 (DIN)
unnamed: LED6.2 (DOUT), LED10.4 (DIN)
unnamed: LED11.2 (DOUT), LED16.4 (DIN)
unnamed: LED7.2 (DOUT), LED11.4 (DIN)
unnamed: LED8.2 (DOUT), LED12.4 (DIN)
unnamed: LED13.2 (DOUT), LED17.4 (DIN)
unnamed: LED9.2 (DOUT), LED13.4 (DIN)
unnamed: LED5.2 (DOUT), LED14.4 (DIN)
unnamed: R1.1, U1.33 (~HWB/PE2)
unnamed: R2.2, U1.3 (D-)
unnamed: R3.2, U1.4 (D+)
unnamed: R6.2, SW1.2, U1.13 (~RESET)
VCC: C3.1, C4.1, C5.1, C6.1, C7.1, J1.A4_B9 (VBUS), J1.B4_A9 (VBUS), LED1.1 (VDD), LED2.1 (VDD), LED3.1 (VDD), LED4.1 (VDD), LED5.1 (VDD), LED6.1 (VDD), LED7.1 (VDD), LED8.1 (VDD), LED9.1 (VDD), LED10.1 (VDD), LED11.1 (VDD), LED12.1 (VDD), LED13.1 (VDD), LED14.1 (VDD), LED15.1 (VDD), LED16.1 (VDD), LED17.1 (VDD), P1.2, R6.1, U1.2 (UVcc), U1.7 (VBus), U1.14 (VCC), U1.24 (AVCC), U1.34 (VCC), U1.44 (AVCC)

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
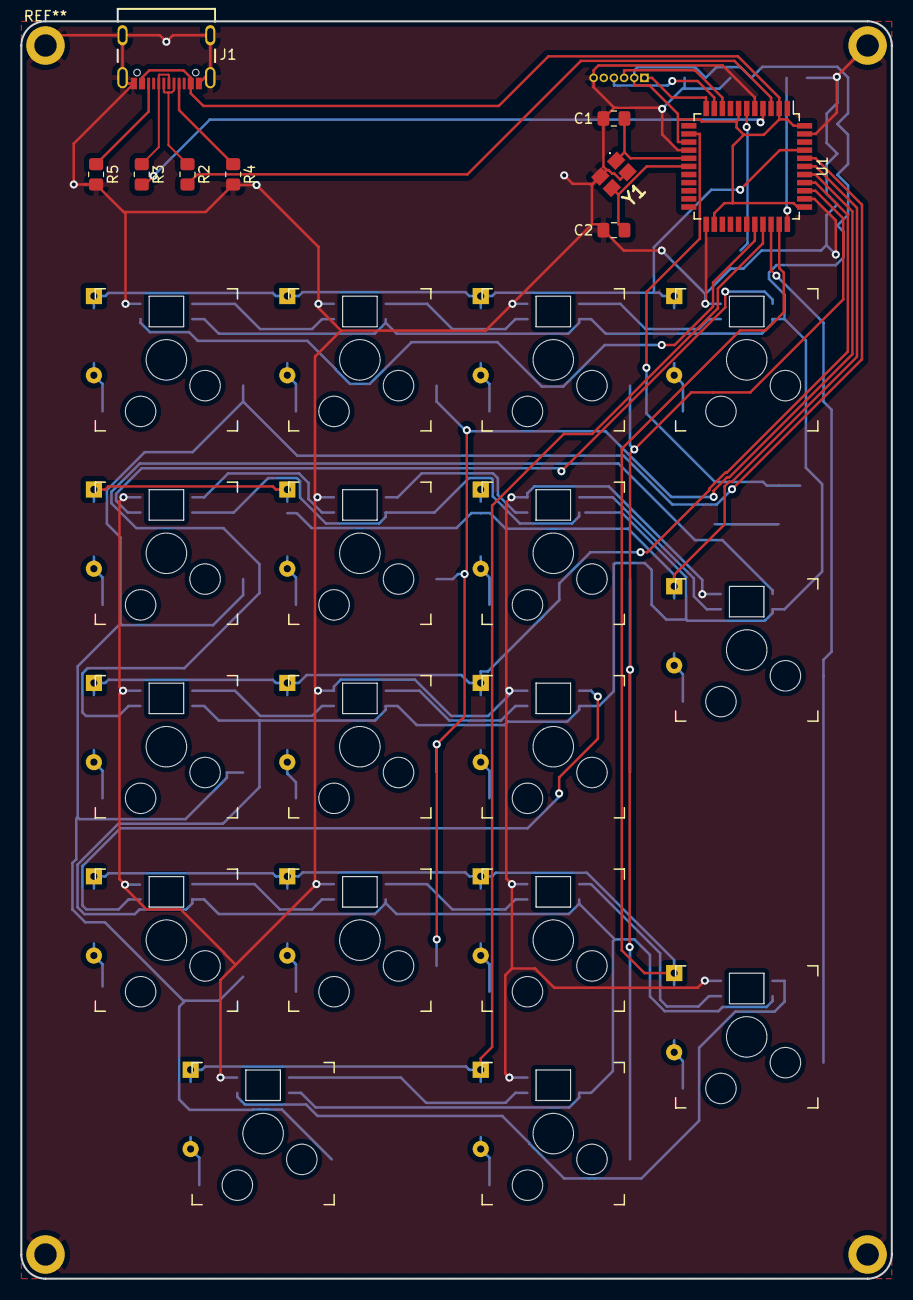
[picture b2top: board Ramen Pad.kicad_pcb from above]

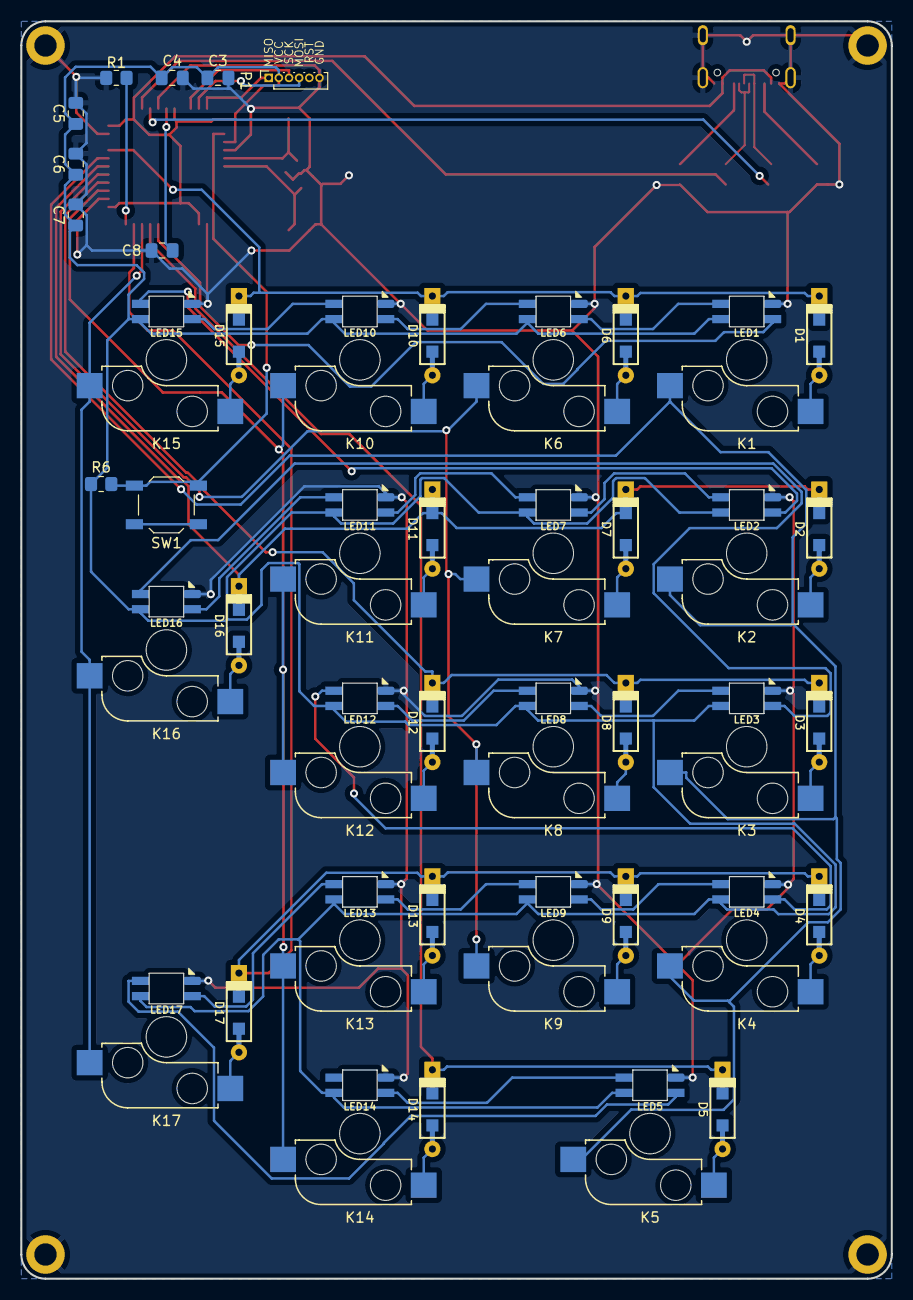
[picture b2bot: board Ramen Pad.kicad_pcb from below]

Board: 2 copper layers, 85.7 x 123.8 mm, 71 parts (44 on the bottom side), 59 nets.

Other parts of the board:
Ramen Pad: LOGO; RamenLogo
